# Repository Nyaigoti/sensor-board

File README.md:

# Custom IoT PCB with ESP32-C3-02 and TP4056 Li-ion Charger

This project involves the design and development of a custom PCB for an IoT application powered by the ESP32-C3-02 SoC. The board includes integrated power management features using the TP4056 Li-ion battery charger IC, enabling efficient and safe charging of a single-cell Li-ion battery.

### Key Features

- **Microcontroller**: ESP32-C3-02 SoC for Wi-Fi and BLE connectivity.
- **Power Management**: TP4056 IC for single-cell Li-ion battery charging with thermal regulation.
- **Battery Protection**: Integrated under-voltage lockout and trickle charging.
- **Sensors and Modules**:
  - BME280 for temperature, humidity, and pressure sensing.
  - Ambient light and sound sensors.
  - Mini SD card reader for data storage.
  - Flash memory for additional storage.
- **Display**: I2C OLED for real-time data visualization.
- **Power Inputs**:
  - USB-C connector for charging and data transfer.
  - LiPo battery connector with onboard charging circuitry.
- **Indicators**: LED indicators for charge status (charging and full).

### Design Highlights

1. **Power Supply Integration**:
   - USB-C provides power for both charging and system operation.
   - TP4056 handles battery charging and protection.
   - Power supplied to the ESP32-C3-02 is regulated for stability.

2. **Modular Architecture**:
   - Supports various sensors and peripherals for IoT applications.
   - Expandable via additional I2C devices.

3. **Safe and Efficient Charging**:
   - Programmable charging current using an external resistor.
   - Automatic charge termination and battery protection.

4. **Compact and Reliable Layout**:
   - Optimized PCB traces for minimal power loss.
   - Thermal management for the TP4056 and other components.

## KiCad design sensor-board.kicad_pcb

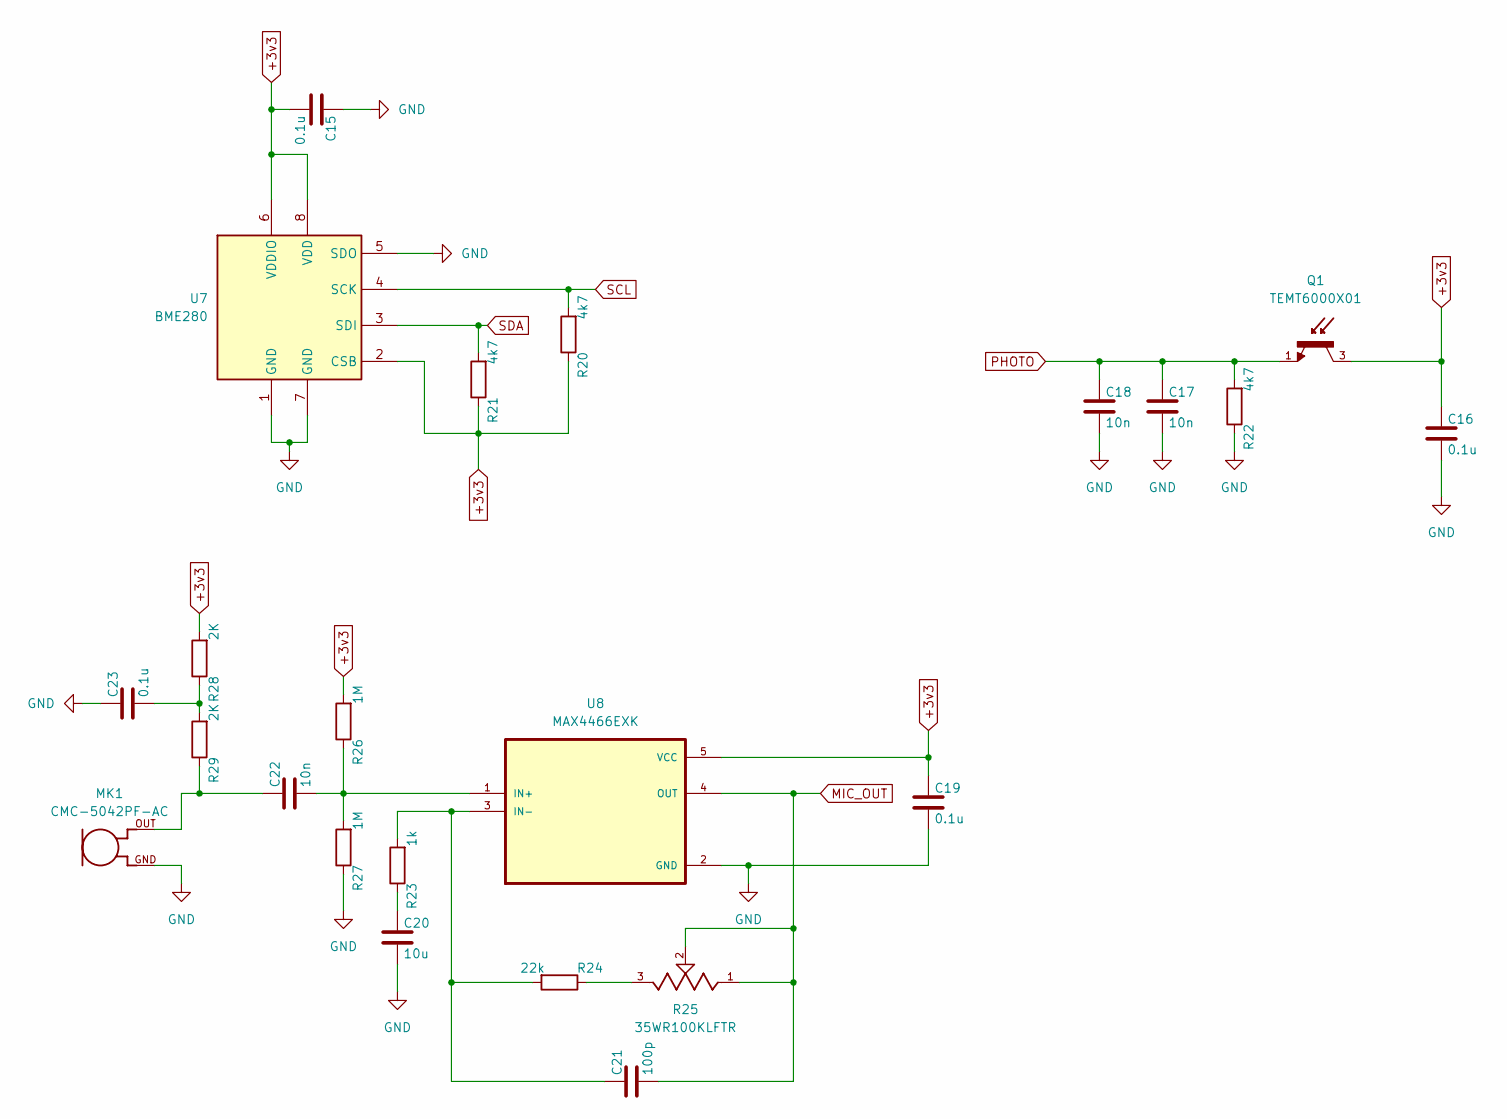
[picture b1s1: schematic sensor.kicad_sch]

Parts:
C15, C16, C19, C23: 0.1u; C_0805_2012Metric
C17, C18, C22: 10n; C_0805_2012Metric
C20: 10u; C_0805_2012Metric
C21: 100p; C_0805_2012Metric
MK1: CMC-5042PF-AC; CUI_CMC-5042PF-AC
Q1: TEMT6000X01; TRANS_TEMT6000X01; PARTREV 1.9
R20, R21, R22: 4k7; R_0805_2012Metric
R23: 1k; R_0805_2012Metric
R24: 22k; R_0805_2012Metric
R25: 35WR100KLFTR; TRIM_35WR100KLFTR; PARTREV D
R26, R27: 1M; R_0805_2012Metric
R28, R29: 2K; R_0805_2012Metric
U7: BME280; Bosch_LGA-8_2.5x2.5mm_P0.65mm_ClockwisePinNumbering
U8: MAX4466EXK; SOT65P210X110-5N

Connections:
+3v3: C15.2, C16.1, C19.1, Q1.3, R20.1, R21.1, R26.2, R28.2, U7.2 (CSB), U7.6 (VDDIO), U7.8 (VDD), U8.5 (VCC); also elsewhere on the board
GND: C15.1, C16.2, C17.2, C18.2, C19.2, C20.2, C23.1, MK1.GND, R22.1, R27.1, U7.1 (GND), U7.5 (SDO), U7.7 (GND), U8.2 (GND); also elsewhere on the board
MIC_OUT: C21.2, R25.1, R25.2, U8.4 (OUT); also elsewhere on the board
unnamed: C20.1, R23.1
unnamed: C22.1, MK1.OUT, R29.1
unnamed: C23.2, R28.1, R29.2
unnamed: R24.1, R25.3
unnamed: C22.2, R26.1, R27.2, U8.1 (IN+)
unnamed: C21.1, R23.2, R24.2, U8.3 (IN-)
PHOTO: C17.1, C18.1, Q1.1, R22.2; also elsewhere on the board
SCL: R20.2, U7.4 (SCK); also elsewhere on the board
SDA: R21.2, U7.3 (SDI); also elsewhere on the board

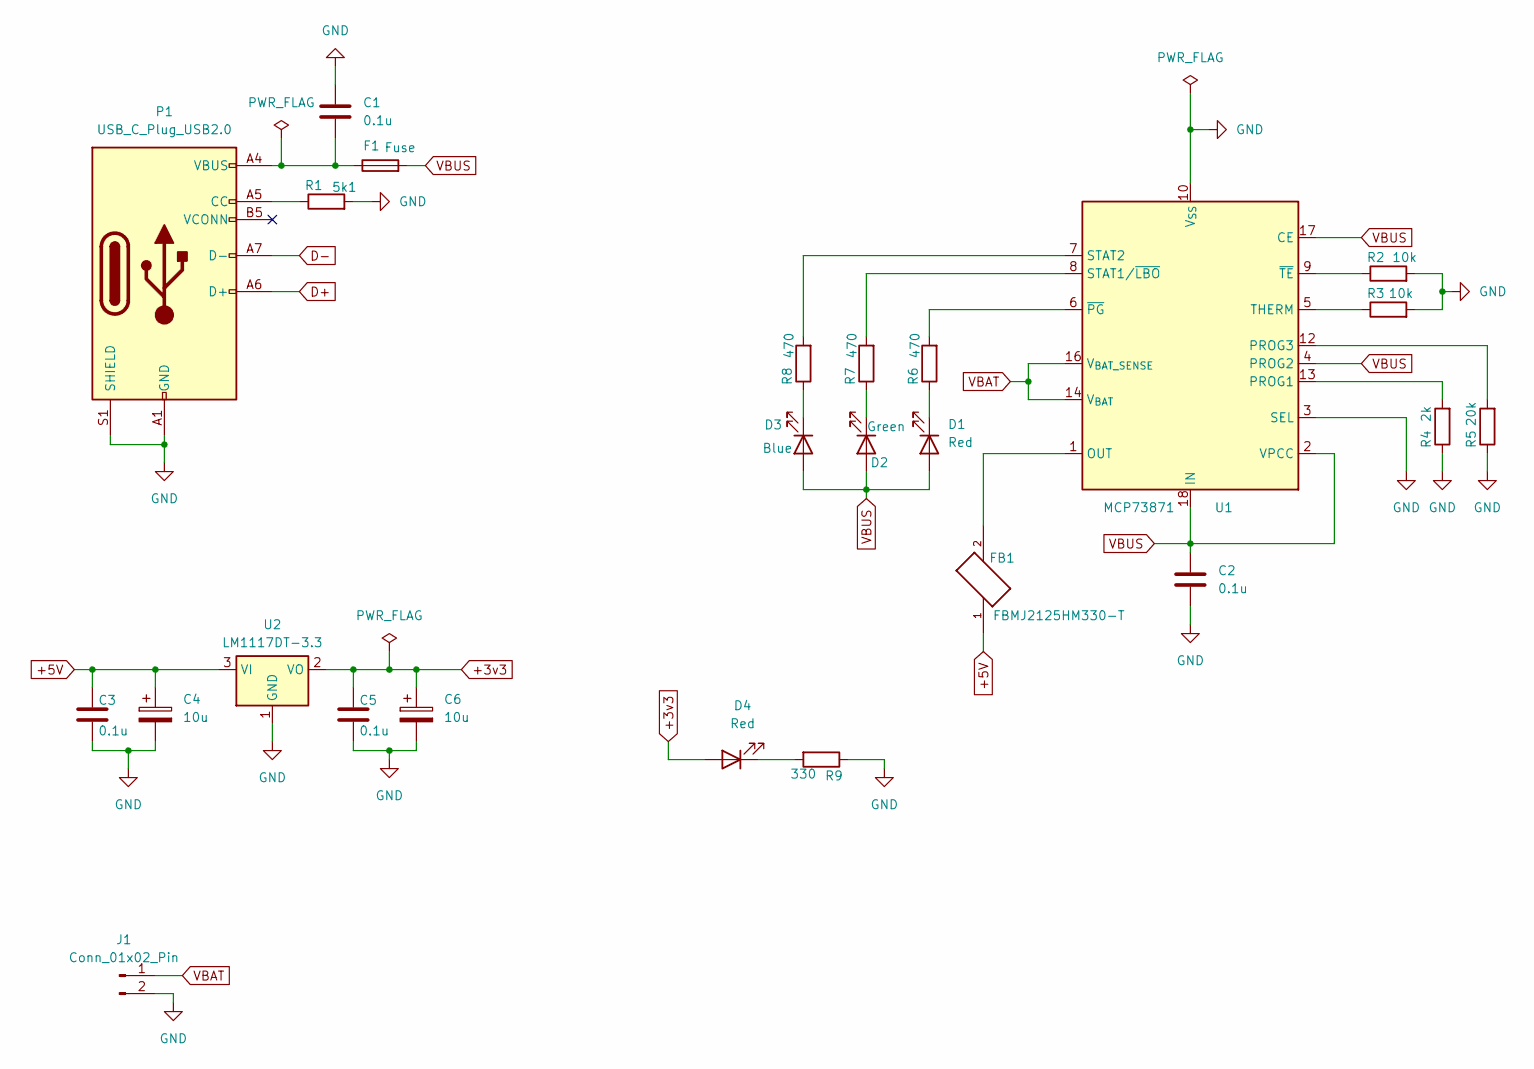
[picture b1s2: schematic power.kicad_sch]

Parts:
C1, C2, C3, C5: 0.1u; C_0805_2012Metric
C4, C6: 10u; C_0805_2012Metric
D1, D4: Red; LED_1206_3216Metric
D2: Green; LED_1206_3216Metric
D3: Blue; LED_1206_3216Metric
F1: Fuse; Fuse_1206_3216Metric
FB1: FBMJ2125HM330-T; BEADC2012X105N
J1: Conn_01x02_Pin; JST_EH_B2B-EH-A_1x02_P2.50mm_Vertical
P1: USB_C_Plug_USB2.0; USB_C_Receptacle_Amphenol_124019772112A
R1: 5k1; R_0805_2012Metric
R2, R3: 10k; R_0805_2012Metric
R4: 2k; R_0805_2012Metric
R5: 20k; R_0805_2012Metric
R6, R7, R8: 470; R_0805_2012Metric
R9: 330; R_0805_2012Metric
U1: MCP73871; QFN-20-1EP_4x4mm_P0.5mm_EP2.5x2.5mm
U2: LM1117DT-3.3; TO-252-3_TabPin2

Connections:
+3v3: C5.1, C6.1, D4.2 (A), U2.2 (VO); also elsewhere on the board
+5V: C3.1, C4.1, FB1.1, U2.3 (VI)
D+: P1.A6 (D+); also elsewhere on the board
D-: P1.A7 (D-); also elsewhere on the board
GND: C1.1, C2.2, C3.2, C4.2, C5.2, C6.2, J1.2, P1.A1 (GND), P1.A12 (GND), P1.B1 (GND), P1.B12 (GND), P1.S1 (SHIELD), R1.2, R2.2, R3.2, R4.1, R5.1, R9.1, U1.3 (SEL), U1.10 (V_{SS}), U1.11 (V_{SS}), U1.21 (V_{SS}), U2.1 (GND); also elsewhere on the board
unnamed: C1.2, F1.1, P1.A4 (VBUS), P1.A9 (VBUS), P1.B4 (VBUS), P1.B9 (VBUS)
unnamed: D1.1 (K), R6.1
unnamed: D2.1 (K), R7.1
unnamed: D3.1 (K), R8.1
unnamed: D4.1 (K), R9.2
unnamed: FB1.2, U1.1 (OUT), U1.20 (OUT)
unnamed: P1.A5 (CC), R1.1
unnamed: R4.2, U1.13 (PROG1)
unnamed: R5.2, U1.12 (PROG3)
unnamed: R7.2, U1.8 (STAT1/~LBO)
unnamed: R8.2, U1.7 (STAT2)
unnamed: R3.1, U1.5 (THERM)
unnamed: R6.2, U1.6 (~PG)
unnamed: R2.1, U1.9 (~TE)
VBAT: J1.1, U1.14 (V_{BAT}), U1.15 (V_{BAT}), U1.16 (V_{BAT_SENSE})
VBUS: C2.1, D1.2 (A), D2.2 (A), D3.2 (A), F1.2, U1.2 (VPCC), U1.4 (PROG2), U1.17 (CE), U1.18 (IN), U1.19 (IN); also elsewhere on the board

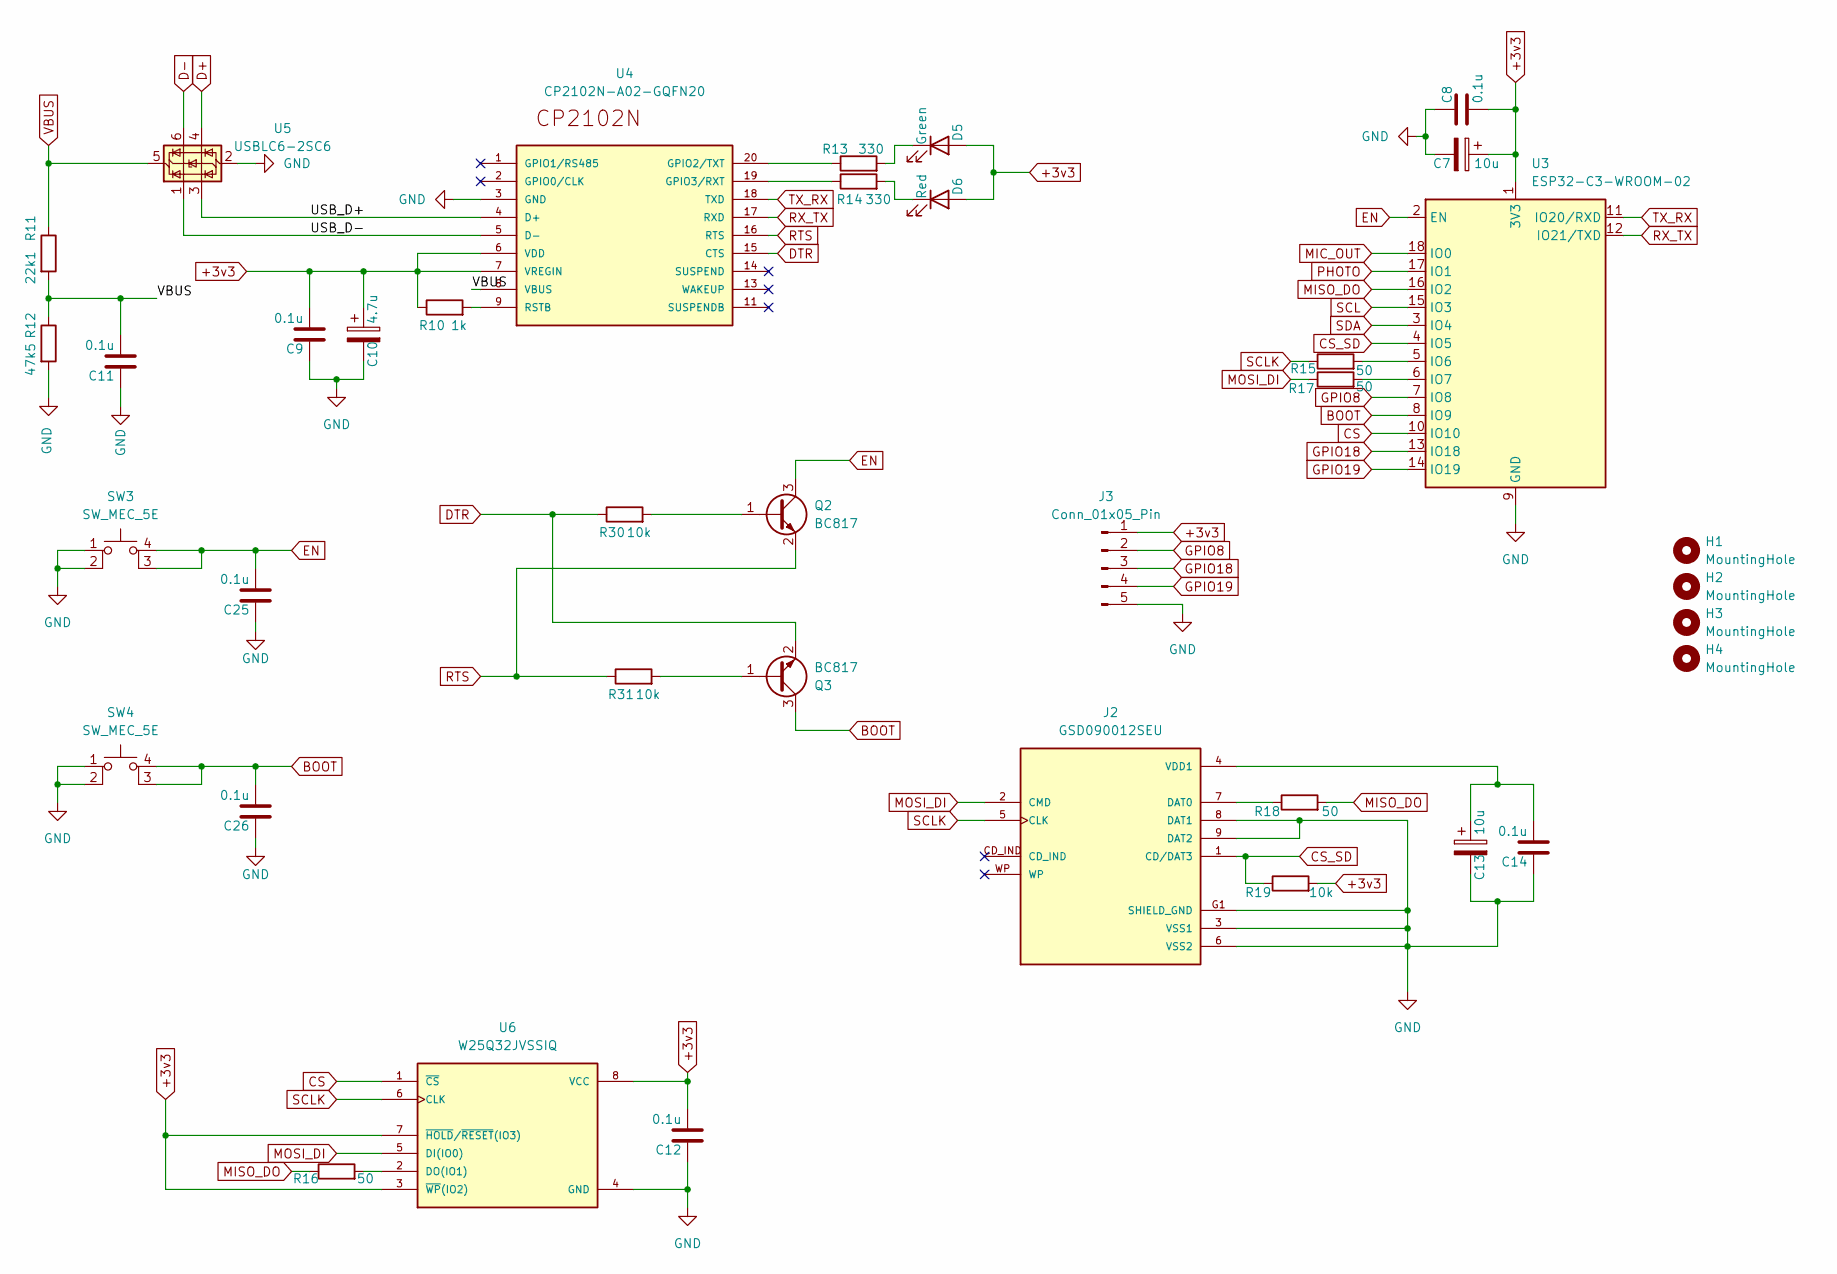
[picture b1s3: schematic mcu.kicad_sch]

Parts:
C7, C13: 10u; C_0805_2012Metric
C8, C9, C11, C12, C14, C25, C26: 0.1u; C_0805_2012Metric
C10: 4.7u; C_0805_2012Metric
D5: Green; LED_1206_3216Metric
D6: Red; LED_1206_3216Metric
H1, H2, H3, H4: MountingHole; MountingHole_2.2mm_M2_DIN965_Pad_TopBottom
J2: GSD090012SEU; AMPHENOL_GSD090012SEU; PARTREV E
J3: Conn_01x05_Pin; PinHeader_1x05_P2.54mm_Vertical_SMD_Pin1Left
Q2, Q3: BC817; SOT-23
R10: 1k; R_0805_2012Metric
R11: 22k1; R_0805_2012Metric
R12: 47k5; R_0805_2012Metric
R13, R14: 330; R_0805_2012Metric
R15, R16, R17, R18: 50; R_0805_2012Metric
R19, R30, R31: 10k; R_0805_2012Metric
SW3, SW4: SW_MEC_5E; SW_USLPT2819DT2TR
U3: ESP32-C3-WROOM-02
U4: CP2102N-A02-GQFN20; WFQFN-20
U5: USBLC6-2SC6; SOT-23-6
U6: W25Q32JVSSIQ; SOIC127P790X216-8N; M_PART_NUMBER W25QXX

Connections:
+3v3: C7.1, C8.2, C9.2, C10.1, C12.2, D5.2 (A), D6.2 (A), J3.1, R10.1, R19.2, U3.1 (3V3), U4.6 (VDD), U4.7 (VREGIN), U6.3 (~WP(IO2)), U6.7 (~HOLD/~RESET(IO3)), U6.8 (VCC); also elsewhere on the board
/mcu/USB_D+: U4.4 (D+), U5.3 (I/O2)
/mcu/USB_D-: U4.5 (D-), U5.1 (I/O1)
BOOT: C26.2, Q3.3 (C), SW4.3 (K), SW4.4 (A), U3.8 (IO9)
CS: U3.10 (IO10), U6.1 (~CS)
CS_SD: J2.1 (CD/DAT3), R19.1, U3.4 (IO5)
D+: U5.4 (I/O2); also elsewhere on the board
D-: U5.6 (I/O1); also elsewhere on the board
DTR: Q3.2 (E), R30.1, U4.15 (CTS)
EN: C25.2, Q2.3 (C), SW3.3 (K), SW3.4 (A), U3.2 (EN)
GND: C7.2, C8.1, C9.1, C10.2, C11.1, C12.1, C13.2, C14.1, C25.1, C26.1, J2.3 (VSS1), J2.6 (VSS2), J2.8 (DAT1), J2.9 (DAT2), J2.G1 (SHIELD_GND), J2.G2 (SHIELD_GND), J2.G3 (SHIELD_GND), J2.G4 (SHIELD_GND), J3.5, R12.2, SW3.1, SW3.2, SW4.1, SW4.2, U3.9 (GND), U3.19 (GND), U4.3 (GND), U4.12 (GND), U4.EXP (GND), U5.2 (GND), U6.4 (GND); also elsewhere on the board
GPIO8: J3.2, U3.7 (IO8)
GPIO18: J3.3, U3.13 (IO18)
GPIO19: J3.4, U3.14 (IO19)
MIC_OUT: U3.18 (IO0); also elsewhere on the board
MISO_DO: R16.1, R18.2, U3.16 (IO2)
MOSI_DI: J2.2 (CMD), R17.1, U6.5 (DI(IO0))
unnamed: D5.1 (K), R13.2
unnamed: D6.1 (K), R14.2
unnamed: J2.7 (DAT0), R18.1
unnamed: C13.1, C14.2, J2.4 (VDD1)
unnamed: Q2.1 (B), R30.2
unnamed: Q3.1 (B), R31.2
unnamed: R15.2, U3.5 (IO6)
unnamed: R17.2, U3.6 (IO7)
unnamed: R13.1, U4.20 (GPIO2/TXT)
unnamed: R14.1, U4.19 (GPIO3/RXT)
unnamed: R10.2, U4.9 (RSTB)
unnamed: R16.2, U6.2 (DO(IO1))
PHOTO: U3.17 (IO1); also elsewhere on the board
RTS: Q2.2 (E), R31.1, U4.16 (RTS)
RX_TX: U3.12 (IO21/TXD), U4.17 (RXD)
SCL: U3.15 (IO3); also elsewhere on the board
SCLK: J2.5 (CLK), R15.1, U6.6 (CLK)
SDA: U3.3 (IO4); also elsewhere on the board
TX_RX: U3.11 (IO20/RXD), U4.18 (TXD)
VBUS: C11.2, R11.1, R11.2, R12.1, U4.8 (VBUS), U5.5 (VBUS); also elsewhere on the board

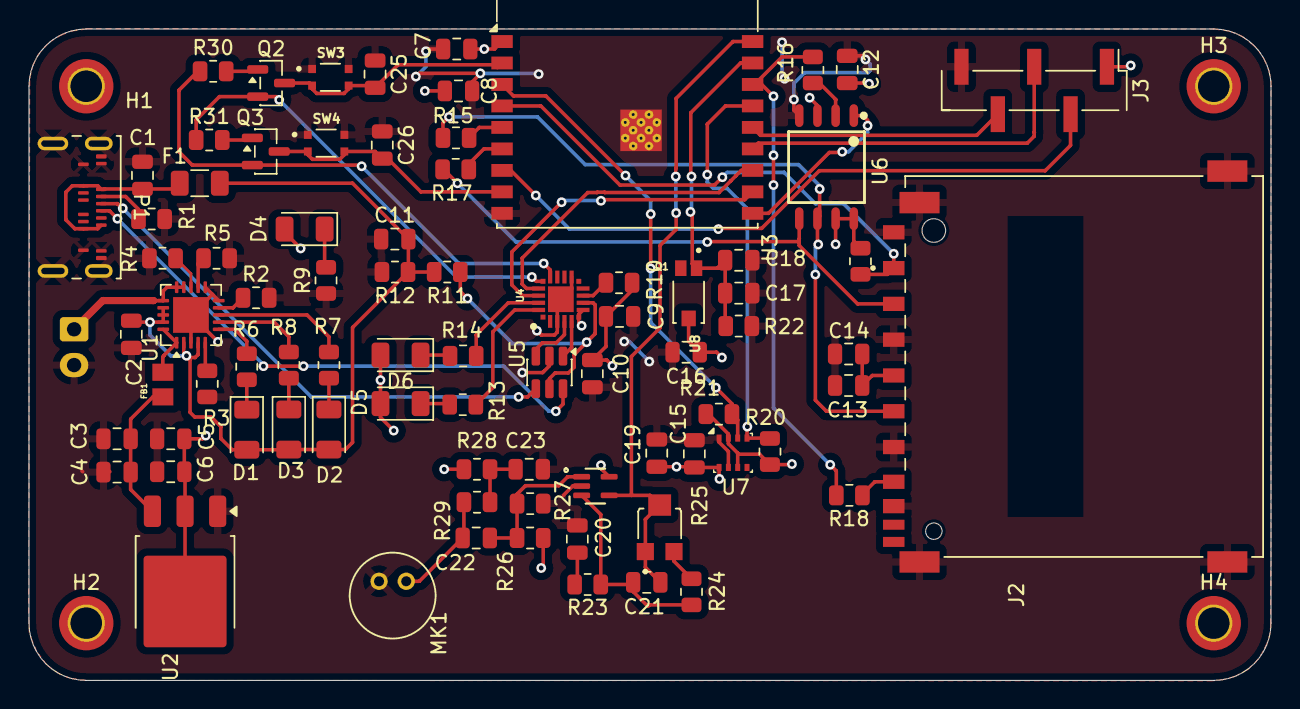
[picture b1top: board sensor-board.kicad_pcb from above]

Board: 2 copper layers, 86.8 x 45.5 mm, 86 parts (1 on the bottom side), 59 nets.
